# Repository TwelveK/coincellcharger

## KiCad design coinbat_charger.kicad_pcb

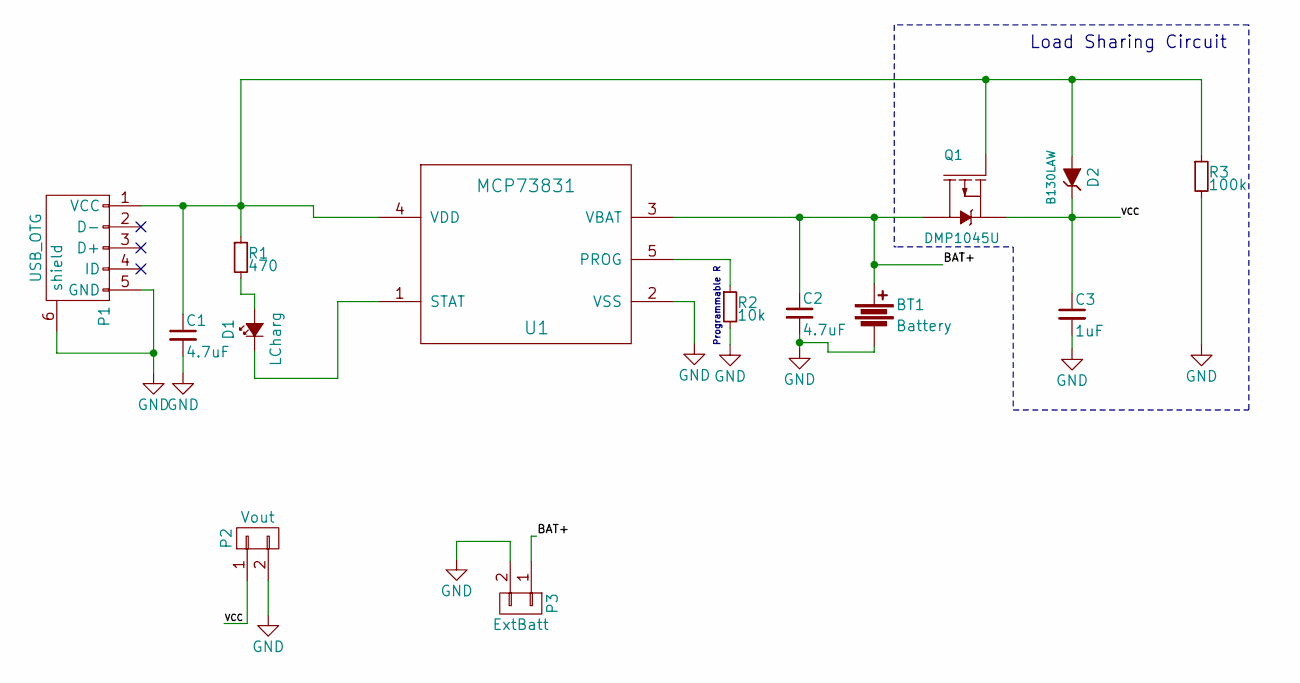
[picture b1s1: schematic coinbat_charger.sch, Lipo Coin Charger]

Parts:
BT1: Battery; LIR2450_keystone_3008
C1, C2: 4.7uF; C_1206_HandSoldering
C3: 1uF; C_1206_HandSoldering
D1: LCharg; LED_1206_HandSoldering
D2: B130LAW; D_SOD-123
P1: USB_OTG; USB_Micro-B_HandSoldering
P2: Vout; Socket_Strip_Straight_1x02_Pitch2.54mm
P3: ExtBatt; Socket_Strip_Straight_1x02_Pitch2.54mm
Q1: DMP1045U; SOT-23_Handsoldering
R1: 470; R_1206_HandSoldering
R2: 10k; R_1206_HandSoldering
R3: 100k; R_1206_HandSoldering
U1: MCP73831; SOT-23-5_HandSoldering

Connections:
/BAT+: BT1.1, C2.1, P3.1, Q1.3 (D), U1.3 (VBAT)
/VCC: C3.1, D2.1 (K), P2.1, Q1.2 (S)
GND: BT1.2, C1.2, C2.2, C3.2, P1.5 (GND), P1.6 (shield), P2.2, P3.2, R2.2, R3.2, U1.2 (VSS)
unnamed: C1.1, D2.2 (A), P1.1 (VCC), Q1.1 (G), R1.1, R3.1, U1.4 (VDD)
unnamed: D1.1 (K), U1.1 (STAT)
unnamed: D1.2 (A), R1.2
unnamed: R2.1, U1.5 (PROG)

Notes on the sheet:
Programmable R
Load Sharing Circuit

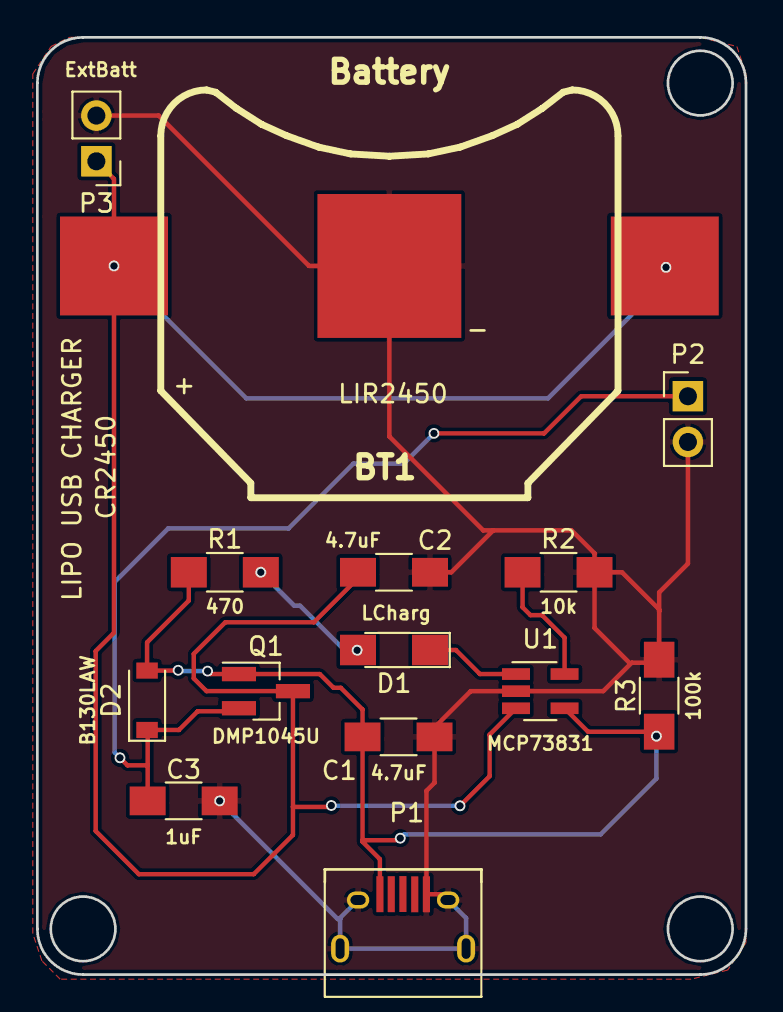
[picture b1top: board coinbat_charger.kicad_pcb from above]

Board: 2 copper layers, 39.4 x 52.1 mm, 14 parts (0 on the bottom side), 7 nets.
